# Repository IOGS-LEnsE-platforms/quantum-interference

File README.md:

# quantum-interference*LEnsE / Institut d'Optique / Dephi Project / 2025*## ReferencesP. Grangier, G. Roger, and A. Aspect, “Experimental Evidence for a Photon Anticorrelation Effect on a Beam Splitter: A New Light on SinglePhoton Interferences”, Europys. Lett. 1 (1986), 173-179, abbreviated GRAin the text.

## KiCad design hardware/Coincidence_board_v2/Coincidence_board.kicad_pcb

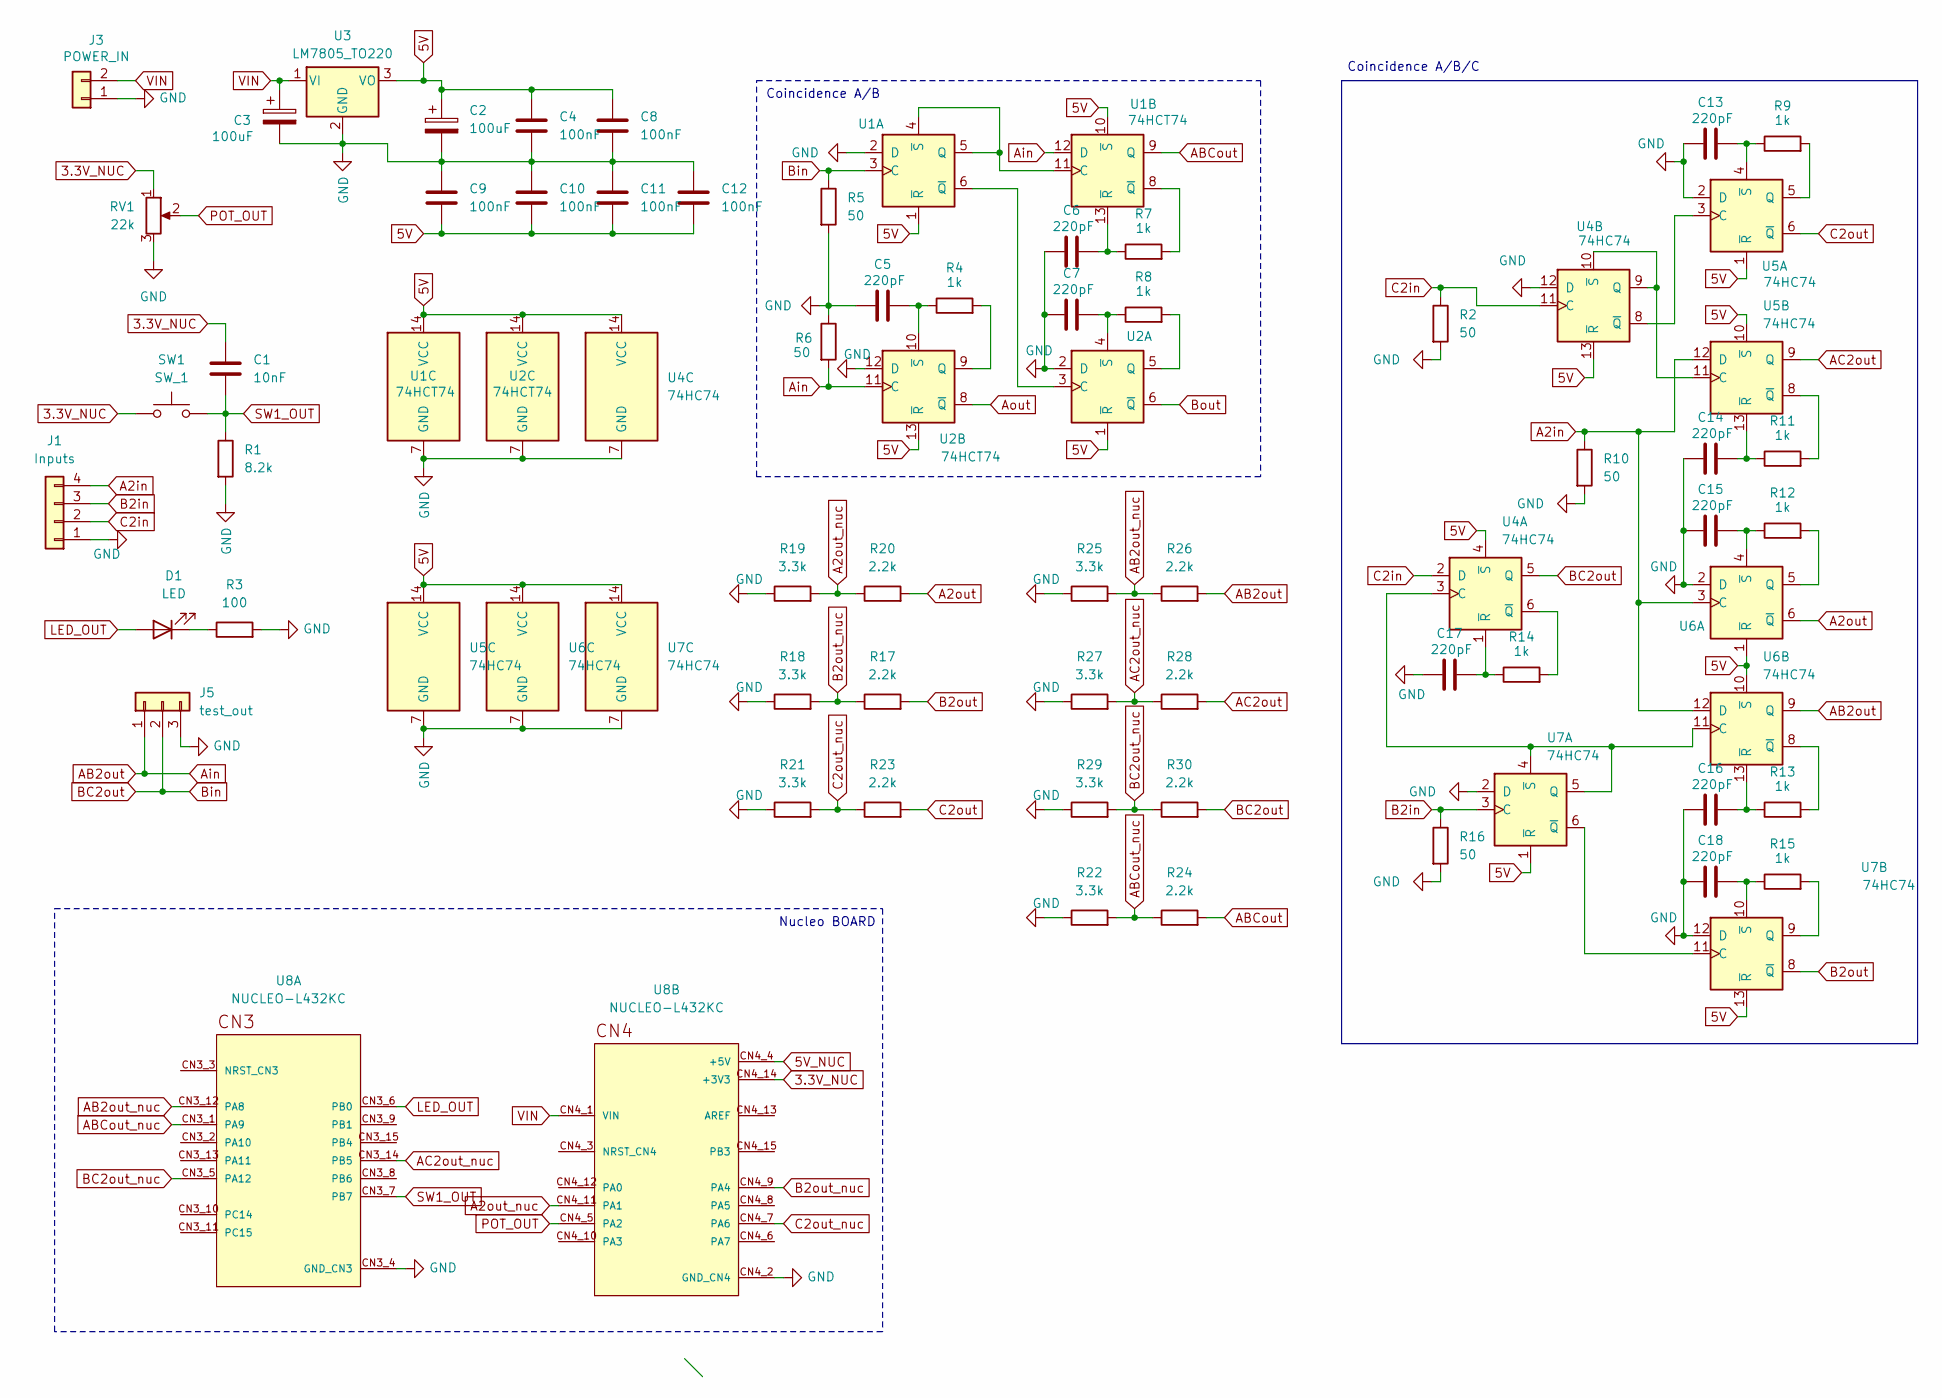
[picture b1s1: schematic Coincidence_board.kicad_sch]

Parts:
C1: 10nF; C_Rect_L7.0mm_W2.5mm_P5.00mm
C2, C3: 100uF; CP_Radial_D6.3mm_P2.50mm
C4, C8, C9, C10, C11, C12: 100nF; C_Rect_L7.0mm_W2.5mm_P5.00mm
C5, C6, C7, C13, C14, C15, C16, C17, C18: 220pF; C_Rect_L4.6mm_W2.0mm_P2.50mm_MKS02_FKP02
D1: LED; LED_D3.0mm_Clear
J1: Inputs; PinHeader_1x04_P2.54mm_Vertical
J3: POWER_IN; TerminalBlock_Phoenix_MKDS-3-2-5.08_1x02_P5.08mm_Horizontal
J5: test_out; PinHeader_1x03_P2.54mm_Vertical
R1: 8.2k; R_Axial_DIN0207_L6.3mm_D2.5mm_P10.16mm_Horizontal
R2, R5, R6, R10, R16: 50; R_Axial_DIN0207_L6.3mm_D2.5mm_P10.16mm_Horizontal
R3: 100; R_Axial_DIN0207_L6.3mm_D2.5mm_P10.16mm_Horizontal
R4, R7, R8, R9, R11, R12, R13, R14, R15: 1k; R_Axial_DIN0207_L6.3mm_D2.5mm_P10.16mm_Horizontal
R17, R20, R23, R24, R26, R28, R30: 2.2k; R_Axial_DIN0207_L6.3mm_D2.5mm_P10.16mm_Horizontal
R18, R19, R21, R22, R25, R27, R29: 3.3k; R_Axial_DIN0207_L6.3mm_D2.5mm_P10.16mm_Horizontal
RV1: 22k; Potentiometer_Bourns_3386P_Vertical
SW1: SW_1; Switch
U1, U2: 74HCT74; DIP-14_W7.62mm_Socket_LongPads
U3: LM7805_TO220; TO-220-3_Vertical
U4, U5, U6, U7: 74HC74; DIP-14_W7.62mm_Socket_LongPads
U8: NUCLEO-L432KC; MODULE_NUCLEO-L432KC; PARTREV N/A

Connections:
3.3V_NUC: C1.1, RV1.1, SW1.1, U8.CN4_14 (+3V3)
5V: C2.1, C4.1, C8.1, C9.2, C10.2, C11.2, C12.2, U1.1 (~R), U1.10 (~S), U1.14 (VCC), U2.1 (~R), U2.13 (~R), U2.14 (VCC), U3.3 (VO), U4.4 (~S), U4.13 (~R), U4.14 (VCC), U5.1 (~R), U5.10 (~S), U5.14 (VCC), U6.1 (~R), U6.10 (~S), U6.14 (VCC), U7.1 (~R), U7.13 (~R), U7.14 (VCC)
5V_NUC: U8.CN4_4 (+5V)
A2in: J1.4, R10.1, U5.12 (D), U6.3 (C), U6.12 (D)
A2out: R20.2, U6.6 (~Q)
A2out_nuc: R19.2, R20.1, U8.CN4_11 (PA1)
AB2out: J5.1, R6.2, R26.2, U1.12 (D), U2.11 (C), U6.9 (Q)
AB2out_nuc: R25.2, R26.1, U8.CN3_12 (PA8)
ABCout: R24.2, U1.9 (Q)
ABCout_nuc: R22.2, R24.1, U8.CN3_1 (PA9)
AC2out: R28.2, U5.9 (Q)
AC2out_nuc: R27.2, R28.1, U8.CN3_14 (PB5)
Aout: U2.8 (~Q)
B2in: J1.3, R16.1, U7.3 (C)
B2out: R17.2, U7.8 (~Q)
B2out_nuc: R17.1, R18.2, U8.CN4_9 (PA4)
BC2out: J5.2, R5.1, R30.2, U1.3 (C), U4.5 (Q)
BC2out_nuc: R29.2, R30.1, U8.CN3_5 (PA12)
Bout: U2.6 (~Q)
C2in: J1.2, R2.1, U4.2 (D), U4.11 (C)
C2out: R23.2, U5.6 (~Q)
C2out_nuc: R21.2, R23.1, U8.CN4_7 (PA6)
GND: C2.2, C3.2, C4.2, C5.1, C6.1, C7.1, C8.2, C9.1, C10.1, C11.1, C12.1, C13.1, C14.1, C15.1, C16.1, C17.1, C18.1, J1.1, J3.1, J5.3, R1.2, R2.2, R3.2, R5.2, R6.1, R10.2, R16.2, R18.1, R19.1, R21.1, R22.1, R25.1, R27.1, R29.1, RV1.3, U1.2 (D), U1.7 (GND), U2.2 (D), U2.7 (GND), U2.12 (D), U3.2 (GND), U4.7 (GND), U4.12 (D), U5.2 (D), U5.7 (GND), U6.2 (D), U6.7 (GND), U7.2 (D), U7.7 (GND), U7.12 (D), U8.CN3_4 (GND_CN3), U8.CN4_2 (GND_CN4)
LED_OUT: D1.2 (A), U8.CN3_6 (PB0)
unnamed: D1.1 (K), R3.1
unnamed: U1.4 (~S), U1.5 (Q), U1.11 (C)
unnamed: U1.6 (~Q), U2.3 (C)
unnamed: R7.2, U1.8 (~Q)
unnamed: C6.2, R7.1, U1.13 (~R)
unnamed: R8.2, U2.5 (Q)
unnamed: C7.2, R8.1, U2.4 (~S)
unnamed: R4.2, U2.9 (Q)
unnamed: C5.2, R4.1, U2.10 (~S)
unnamed: U4.3 (C), U6.11 (C), U7.4 (~S), U7.5 (Q)
unnamed: R14.2, U4.6 (~Q)
unnamed: C17.2, R14.1, U4.1 (~R)
unnamed: U4.9 (Q), U4.10 (~S), U5.11 (C)
unnamed: U4.8 (~Q), U5.3 (C)
unnamed: R9.2, U5.5 (Q)
unnamed: C13.2, R9.1, U5.4 (~S)
unnamed: R11.2, U5.8 (~Q)
unnamed: C14.2, R11.1, U5.13 (~R)
unnamed: R12.2, U6.5 (Q)
unnamed: C15.2, R12.1, U6.4 (~S)
unnamed: R13.2, U6.8 (~Q)
unnamed: C16.2, R13.1, U6.13 (~R)
unnamed: U7.6 (~Q), U7.11 (C)
unnamed: R15.2, U7.9 (Q)
unnamed: C18.2, R15.1, U7.10 (~S)
POT_OUT: RV1.2, U8.CN4_5 (PA2)
SW1_OUT: C1.2, R1.1, SW1.2, U8.CN3_7 (PB7)
VIN: C3.1, J3.2, U3.1 (VI), U8.CN4_1 (VIN)

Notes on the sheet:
Coincidence A/B
Coincidence A/B/C
Nucleo BOARD

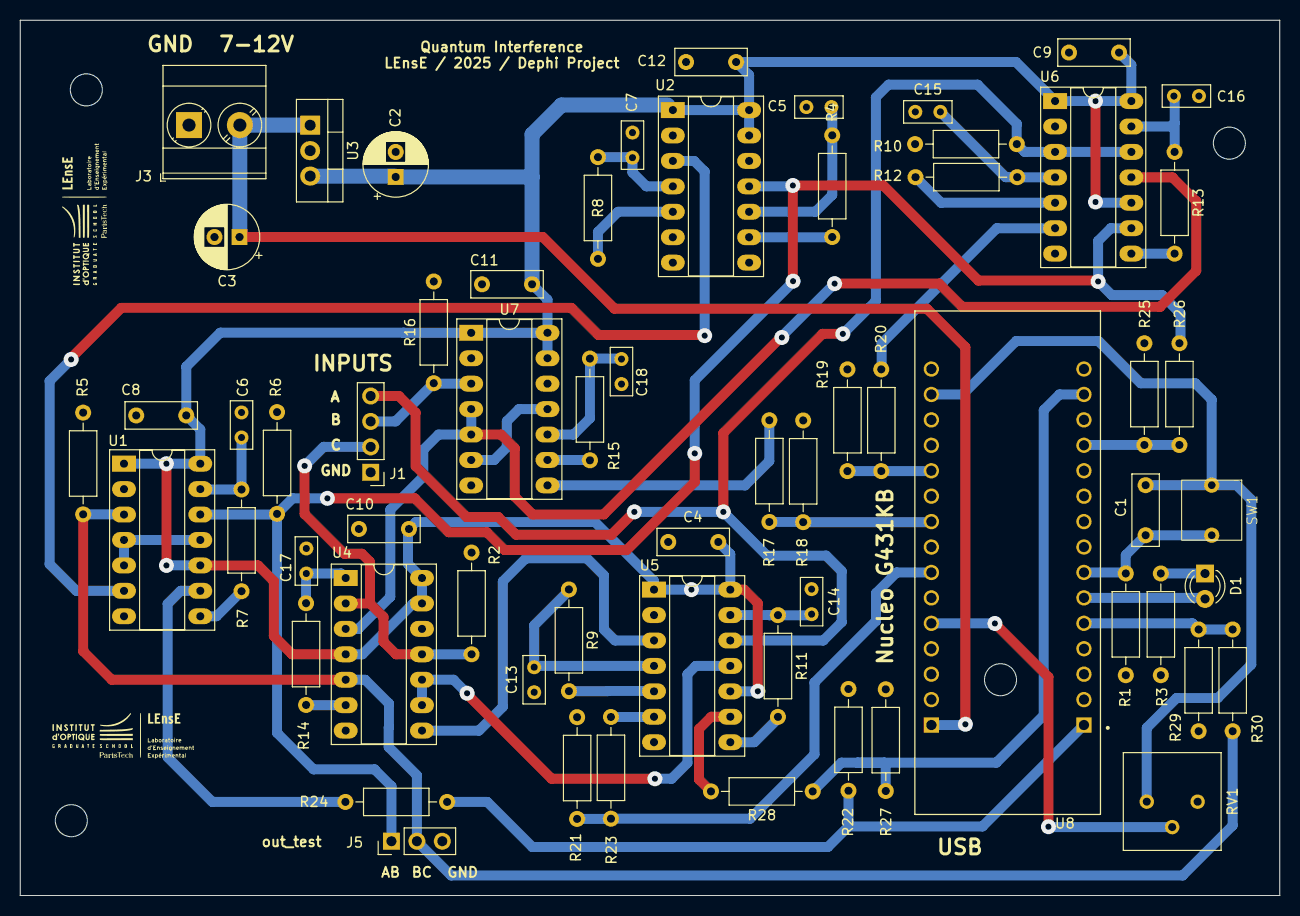
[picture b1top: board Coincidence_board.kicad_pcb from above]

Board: 2 copper layers, 125.8 x 87.4 mm, 64 parts (0 on the bottom side), 49 nets.

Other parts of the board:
M: MountingHole_3.2mm_M3
M#2: MountingHole_3.2mm_M3

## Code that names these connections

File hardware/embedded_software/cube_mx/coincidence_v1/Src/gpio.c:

/* USER CODE BEGIN Header */
/**
  ******************************************************************************
  * @file    gpio.c
  * @brief   This file provides code for the configuration
  *          of all used GPIO pins.
  ******************************************************************************
  * @attention
  *
  * Copyright (c) 2025 STMicroelectronics.
  * All rights reserved.
  *
  * This software is licensed under terms that can be found in the LICENSE file
  * in the root directory of this software component.
  * If no LICENSE file comes with this software, it is provided AS-IS.
  *
  ******************************************************************************
  */
/* USER CODE END Header */

/* Includes ------------------------------------------------------------------*/
#include "gpio.h"

/* USER CODE BEGIN 0 */

/* USER CODE END 0 */

/*----------------------------------------------------------------------------*/
/* Configure GPIO                                                             */
/*----------------------------------------------------------------------------*/
/* USER CODE BEGIN 1 */

/* USER CODE END 1 */

/** Configure pins as
        * Analog
        * Input
        * Output
        * EVENT_OUT
        * EXTI
*/
void MX_GPIO_Init(void)
{

  GPIO_InitTypeDef GPIO_InitStruct = {0};

  /* GPIO Ports Clock Enable */
  __HAL_RCC_GPIOA_CLK_ENABLE();
  __HAL_RCC_GPIOB_CLK_ENABLE();

  /*Configure GPIO pin Output Level */
  HAL_GPIO_WritePin(GPIOB, GPIO_PIN_4|LD2_Pin, GPIO_PIN_RESET);

  /*Configure GPIO pins : PA1 PA4 PA6 PA8
                           PA9 PA12 */
  GPIO_InitStruct.Pin = GPIO_PIN_1|GPIO_PIN_4|GPIO_PIN_6|GPIO_PIN_8
                          |GPIO_PIN_9|GPIO_PIN_12;
  GPIO_InitStruct.Mode = GPIO_MODE_IT_RISING;
  GPIO_InitStruct.Pull = GPIO_NOPULL;
  HAL_GPIO_Init(GPIOA, &GPIO_InitStruct);

  /*Configure GPIO pins : PB4 LD2_Pin */
  GPIO_InitStruct.Pin = GPIO_PIN_4|LD2_Pin;
  GPIO_InitStruct.Mode = GPIO_MODE_OUTPUT_PP;
  GPIO_InitStruct.Pull = GPIO_NOPULL;
  GPIO_InitStruct.Speed = GPIO_SPEED_FREQ_LOW;
  HAL_GPIO_Init(GPIOB, &GPIO_InitStruct);

  /*Configure GPIO pin : PB5 */
  GPIO_InitStruct.Pin = GPIO_PIN_5;
  GPIO_InitStruct.Mode = GPIO_MODE_IT_RISING;
  GPIO_InitStruct.Pull = GPIO_NOPULL;
  HAL_GPIO_Init(GPIOB, &GPIO_InitStruct);

  /* EXTI interrupt init*/
  HAL_NVIC_SetPriority(EXTI1_IRQn, 0, 0);
  HAL_NVIC_EnableIRQ(EXTI1_IRQn);

  HAL_NVIC_SetPriority(EXTI4_IRQn, 0, 0);
  HAL_NVIC_EnableIRQ(EXTI4_IRQn);

  HAL_NVIC_SetPriority(EXTI9_5_IRQn, 0, 0);
  HAL_NVIC_EnableIRQ(EXTI9_5_IRQn);

  HAL_NVIC_SetPriority(EXTI15_10_IRQn, 0, 0);
  HAL_NVIC_EnableIRQ(EXTI15_10_IRQn);

}

/* USER CODE BEGIN 2 */

/* USER CODE END 2 */

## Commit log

2024-11-06 Update Files / Adding Arduino Code for Nucleo board for rate testing
2024-11-06 Update Coincidence Board / Dephi 2024
2024-11-07 Update Schematics of Electronic Board
2024-11-07 Update Test on Nucleo Board - up to 80kHz !!
2024-11-08 Update Schematic
2025-03-06 Update Coincidence Board / New schematics (Anouk - Jeanne)
    Test with Nucleo L476RG ? Not fast enough ??
2025-03-06 Update Coincidence Board / 2025 version
2025-03-07 Create CubeIDE project for STM32 Nucleo board / G431KB
2025-03-07 Update Small
2025-03-08 Update MXIDE code / Adding USART2 transmission of characters / Tested on G431KB and TeraTerm
2025-03-08 Update Embedded program / STM32CubeIDE / HAL version with 7 EXTI !
    Need to test on 7 inputs / Max frequency ?
2025-03-10 Update Quantum
2025-03-10 Update Coincidence Board / v2
2025-03-10 Update GRA experiment / Creating new electronic interface based on G431KB Nucleo board
2025-03-12 Update Board v2 / Before sending to JLCPCB
2025-03-29 Update FIR Filter on G431KB / FIR code in STM32CubeIde and MX
2025-03-30 Update Program
2025-03-30 Update Cube_MX program
2025-05-15 Adding Code from DePhi
2025-07-16 Add 2025 projects from students
